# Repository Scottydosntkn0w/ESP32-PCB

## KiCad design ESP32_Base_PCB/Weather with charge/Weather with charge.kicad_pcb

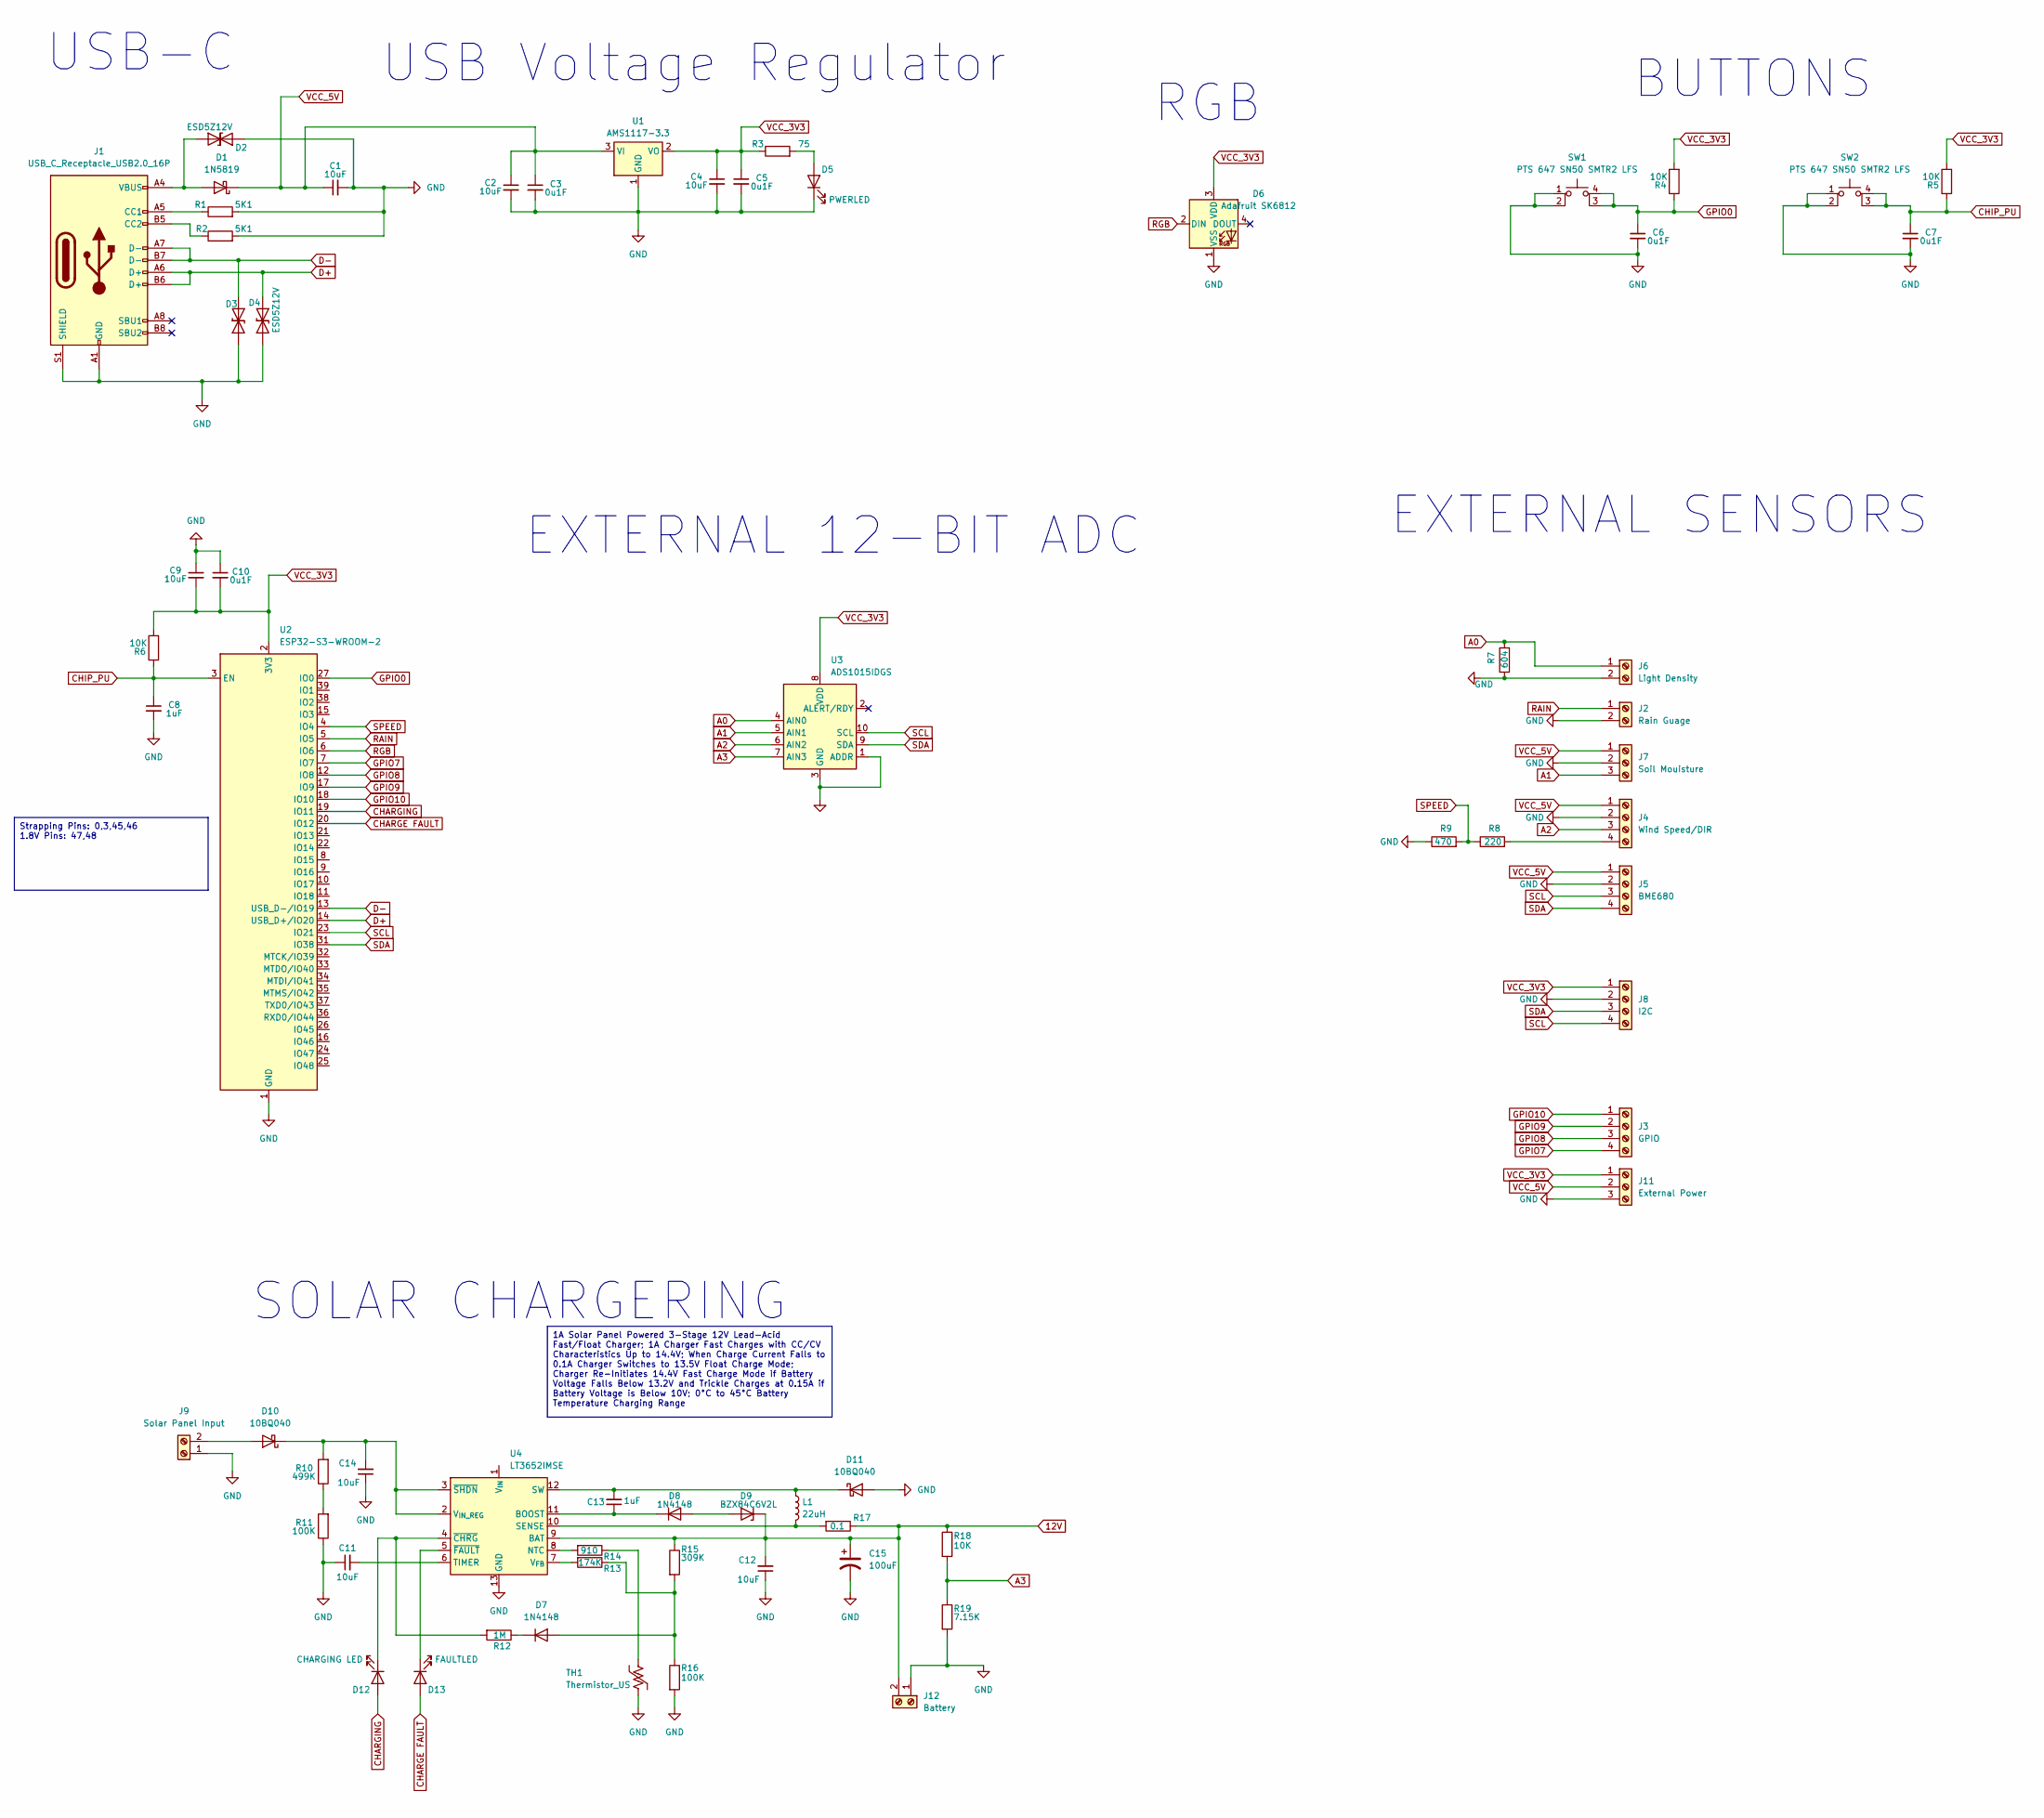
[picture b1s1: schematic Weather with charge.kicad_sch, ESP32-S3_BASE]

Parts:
C1, C2, C4, C9, C11, C12, C14: 10uF; C_0805_2012Metric_Pad1.18x1.45mm_HandSolder; Manufacturer_Part_Number 0805W106K500CC
C3, C5, C6, C7, C10: 0u1F; C_0805_2012Metric_Pad1.18x1.45mm_HandSolder; Manufacturer_Part_Number 0805B104K101CC
C8: 1uF; C_0805_2012Metric_Pad1.18x1.45mm_HandSolder; Manufacturer_Part_Number 0805B105K250DC
C13: 1uF; C_0805_2012Metric_Pad1.18x1.45mm_HandSolder; Manufacturer_Part_Number 0805W106K500CC
C15: 100uF
D1: 1N5819; D_DO-41_SOD81_P10.16mm_Horizontal; Manufacturer_Part_Number 1N5819
D2, D3, D4: ESD5Z12V; D_SOD-523; Manufacturer_Part_Number ESD5Z12V
D5: PWERLED; LED_0603_1608Metric; Manufacturer_Part_Number 0603GBD0790S01
D6: Adafruit SK6812; LED_SK6812_PLCC4_5.0x5.0mm_P3.2mm; Manufacturer_Part_Number 1655
D7, D8: 1N4148; D_DO-35_SOD27_P7.62mm_Horizontal
D9: BZX84C6V2L; SOT-23
D10, D11: 10BQ040; D_SMA; Manufacturer_Part_Number 10BQ040
D12: CHARGING LED; LED_0603_1608Metric; Manufacturer_Part_Number 0603GBD0790S01
D13: FAULTLED; LED_0603_1608Metric; Manufacturer_Part_Number 0603GBD0790S01
J1: USB_C_Receptacle_USB2.0_16P; USB_C_Receptacle_GCT_USB4105-xx-A_16P_TopMnt_Horizontal; Manufacturer_Part_Number USB4105-GF-A
J2: Rain Guage; TerminalBlock_Phoenix_MKDS-1,5-2-5.08_1x02_P5.08mm_Horizont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; Manufacturer_Part_Number 282837-2
J3: GPIO; TerminalBlock_Phoenix_MKDS-1,5-4-5.08_1x04_P5.08mm_Horizont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; Manufacturer_Part_Number 282837-4
J4: Wind Speed/DIR; TerminalBlock_Phoenix_MKDS-1,5-4-5.08_1x04_P5.08mm_Horizont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; Manufacturer_Part_Number 282837-4
J5: BME680; TerminalBlock_Phoenix_MKDS-1,5-4-5.08_1x04_P5.08mm_Horizont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; Manufacturer_Part_Number 282837-4
J6: Light Density; TerminalBlock_Phoenix_MKDS-1,5-2-5.08_1x02_P5.08mm_Horizont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; Manufacturer_Part_Number 282837-2
J7: Soil Mouisture; TerminalBlock_Phoenix_MKDS-1,5-3-5.08_1x03_P5.08mm_Horizont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; Manufacturer_Part_Number 282837-3
J8: I2C; TerminalBlock_Phoenix_MKDS-1,5-4-5.08_1x04_P5.08mm_Horizont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; Manufacturer_Part_Number 282837-4
J9: Solar Panel Input; TerminalBlock_Phoenix_MKDS-1,5-2-5.08_1x02_P5.08mm_Horizont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; Manufacturer_Part_Number 282837-2
J11: External Power; TerminalBlock_Phoenix_MKDS-1,5-3-5.08_1x03_P5.08mm_Horizont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; Manufacturer_Part_Number 282837-3
J12: Battery; TerminalBlock_Phoenix_MKDS-1,5-2-5.08_1x02_P5.08mm_Horizont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; Manufacturer_Part_Number 282837-2
L1: 22uH; Manufacturer_Part_Number 7447779122
R1, R2: 5K1; R_0603_1608Metric_Pad0.98x0.95mm_HandSolder; Manufacturer_Part_Number RC0603FR-075K1L
R3: 75; R_0603_1608Metric_Pad0.98x0.95mm_HandSolder; Manufacturer_Part_Number RC0603FR-0775RL
R4, R5, R6: 10K; R_0603_1608Metric_Pad0.98x0.95mm_HandSolder; Manufacturer_Part_Number RC0603FR-0710KL
R7: 604; R_Axial_DIN0207_L6.3mm_D2.5mm_P10.16mm_Horizontal
R8: 220; R_0603_1608Metric_Pad0.98x0.95mm_HandSolder; Manufacturer_Part_Number RMCF0603JT220R
R9: 470; R_0603_1608Metric_Pad0.98x0.95mm_HandSolder; Manufacturer_Part_Number RL0603FR-070R47L
R10: 499K; R_0603_1608Metric_Pad0.98x0.95mm_HandSolder; Manufacturer_Part_Number RC0603FR-0775RL
R11, R16: 100K; R_0603_1608Metric_Pad0.98x0.95mm_HandSolder; Manufacturer_Part_Number RC0603FR-0775RL
R12: 1M; R_0603_1608Metric_Pad0.98x0.95mm_HandSolder; Manufacturer_Part_Number RC0603FR-0775RL
R13: 174K; R_0603_1608Metric_Pad0.98x0.95mm_HandSolder; Manufacturer_Part_Number RC0603FR-0775RL
R14: 910; R_0603_1608Metric_Pad0.98x0.95mm_HandSolder; Manufacturer_Part_Number RC0603FR-0775RL
R15: 309K; R_0603_1608Metric_Pad0.98x0.95mm_HandSolder; Manufacturer_Part_Number RC0603FR-0775RL
R17: 0.1; R_0603_1608Metric_Pad0.98x0.95mm_HandSolder; Manufacturer_Part_Number RC0603FR-0775RL
R18: 10K; R_0603_1608Metric_Pad0.98x0.95mm_HandSolder; Manufacturer_Part_Number RC0603FR-0775RL
R19: 7.15K; R_0603_1608Metric_Pad0.98x0.95mm_HandSolder; Manufacturer_Part_Number RC0603FR-0775RL
SW1, SW2: PTS 647 SN50 SMTR2 LFS; SW_PTS_647_SN50_SMTR2_LFS; Manufacturer_Part_Number PTS 647 SN50 SMTR2 LFS
TH1: Thermistor_US; R_0603_1608Metric; Manufacturer_Part_Number NCP18XH103F0SRB
U1: AMS1117-3.3; SOT-223-3_TabPin2; Manufacturer_Part_Number AMS1117-3.3
U2: ESP32-S3-WROOM-2; Manufacturer_Part_Number ESP32-S3-WROOM-2-N32R8V
U3: ADS1015IDGS; TSSOP-10_3x3mm_P0.5mm; Manufacturer_Part_Number ADS1015IDGS
U4: LT3652IMSE; MSOP-12-1EP_3x4mm_P0.65mm_EP1.65x2.85mm; Manufacturer_Part_Number LT3652HVIMSE#TRPBF

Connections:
12V: C12.2, C15.1, D9.3 (K), J12.2, R15.1, R17.1, R18.1, U4.9 (BAT)
A0: J6.1, R7.2, U3.4 (AIN0)
A1: J7.3, U3.5 (AIN1)
A2: J4.3, U3.6 (AIN2)
A3: R18.2, R19.1, U3.7 (AIN3); also elsewhere on the board
CHARGE FAULT: D13.1 (K), D13.2 (A), U2.20 (IO12), U4.5 (~FAULT)
CHIP_PU: C7.1, C8.1, R5.1, R6.1, SW2.3 (K), SW2.4 (A), U2.3 (EN)
D+: D4.2 (A), J1.A6 (D+), J1.B6 (D+), U2.14 (USB_D+/IO20)
D-: D3.2 (A), J1.A7 (D-), J1.B7 (D-), U2.13 (USB_D-/IO19)
GND: C1.2, C2.2, C3.2, C4.2, C5.2, C6.2, C7.2, C8.2, C9.1, C10.1, C11.1, C12.1, C14.1, C15.2, D2.1 (K), D3.1 (K), D4.1 (K), D5.1 (K), D6.1 (VSS), D11.2 (A), J1.A1 (GND), J1.A12 (GND), J1.B1 (GND), J1.B12 (GND), J1.S1 (SHIELD), J2.2, J4.2, J5.2, J6.2, J7.2, J8.2, J9.1, J11.3, J12.1, R1.2, R2.2, R7.1, R9.1, R11.1, R16.2, R19.2, SW1.1, SW1.2, SW2.1, SW2.2, TH1.2, U1.1 (GND), U2.1 (GND), U2.40 (GND), U2.41 (GND), U3.1 (ADDR), U3.3 (GND), U4.13 (GND); also elsewhere on the board
GPIO0: C6.1, R4.1, SW1.3 (K), SW1.4 (A), U2.27 (IO0)
GPIO7: J3.4, U2.7 (IO7)
GPIO8: J3.3, U2.12 (IO8)
GPIO9: J3.2, U2.17 (IO9)
GPIO10: J3.1, U2.18 (IO10)
unnamed: D1.2 (A), D2.2 (A), J1.A4 (VBUS), J1.A9 (VBUS), J1.B4 (VBUS), J1.B9 (VBUS)
unnamed: D5.2 (A), R3.2
unnamed: D7.2 (A), R13.1, R15.2, R16.1
unnamed: D7.1 (K), R12.1
unnamed: D8.2 (A), D9.1 (A)
unnamed: C13.1, D8.1 (K), U4.11 (BOOST)
unnamed: D10.2 (A), J9.2
unnamed: C14.2, D10.1 (K), R10.2, U4.2 (V_{IN_REG}), U4.3 (~SHDN)
unnamed: C13.2, D11.1 (K), L1.1, U4.12 (SW)
unnamed: J1.A5 (CC1), R1.1
unnamed: J1.B5 (CC2), R2.1
unnamed: J4.4, R8.2
unnamed: R10.1, R11.2
unnamed: R14.1, TH1.1
unnamed: R14.2, U4.8 (NTC)
unnamed: L1.2, R17.2, U4.10 (SENSE)
unnamed: C11.2, U4.6 (TIMER)
unnamed: R13.2, U4.7 (V_{FB})
RAIN: J2.1, U2.5 (IO5)
RGB: D6.2 (DIN), U2.6 (IO6)
SCL: J5.3, J8.4, U2.23 (IO21), U3.10 (SCL)
SDA: J5.4, J8.3, U2.31 (IO38), U3.9 (SDA)
SPEED: R8.1, R9.2, U2.4 (IO4)
VCC_3V3: C4.1, C5.1, C9.2, C10.2, D6.3 (VDD), J8.1, J11.1, R3.1, R4.2, R5.2, R6.2, U1.2 (VO), U2.2 (3V3), U3.8 (VDD)
VCC_5V: C1.1, C2.1, C3.1, D1.1 (K), J4.1, J5.1, J7.1, J11.2, U1.3 (VI); also elsewhere on the board

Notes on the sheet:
1A Solar Panel Powered 3-Stage 12V Lead-Acid Fast/Float Charger; 1A Charger Fast Charges with CC/CV Characteristics Up to 14.4V; When Charge Current Falls to 0.1A Charger Switches to 13.5V Float Charge Mode; Charger Re-Initiates 14.4V Fast Charge Mode if Battery Voltage Falls Below 13.2V and Trickl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
Strapping Pins: 0,3,45,46 1.8V Pins: 47,48
USB-C
RGB
EXTERNAL SENSORS
SOLAR CHARGERING
USB Voltage Regulator
BUTTONS
EXTERNAL 12-BIT ADC

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
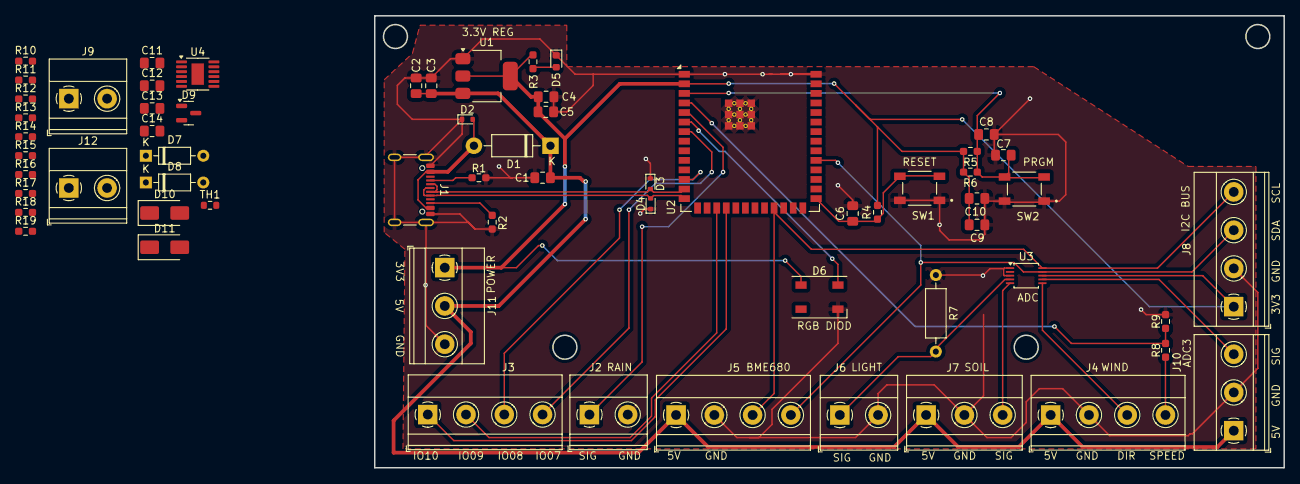
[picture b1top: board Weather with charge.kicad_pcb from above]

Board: 2 copper layers, 120.8 x 60.0 mm, 63 parts (0 on the bottom side), 41 nets.

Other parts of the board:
J10: A3 of ADC; TerminalBlock_Phoenix_MKDS-1,5-3-5.08_1x03_P5.08mm_Horizont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

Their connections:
A3: J10.3; also elsewhere on the board
GND: J10.2; also elsewhere on the board
VCC_5V: J10.1; also elsewhere on the board

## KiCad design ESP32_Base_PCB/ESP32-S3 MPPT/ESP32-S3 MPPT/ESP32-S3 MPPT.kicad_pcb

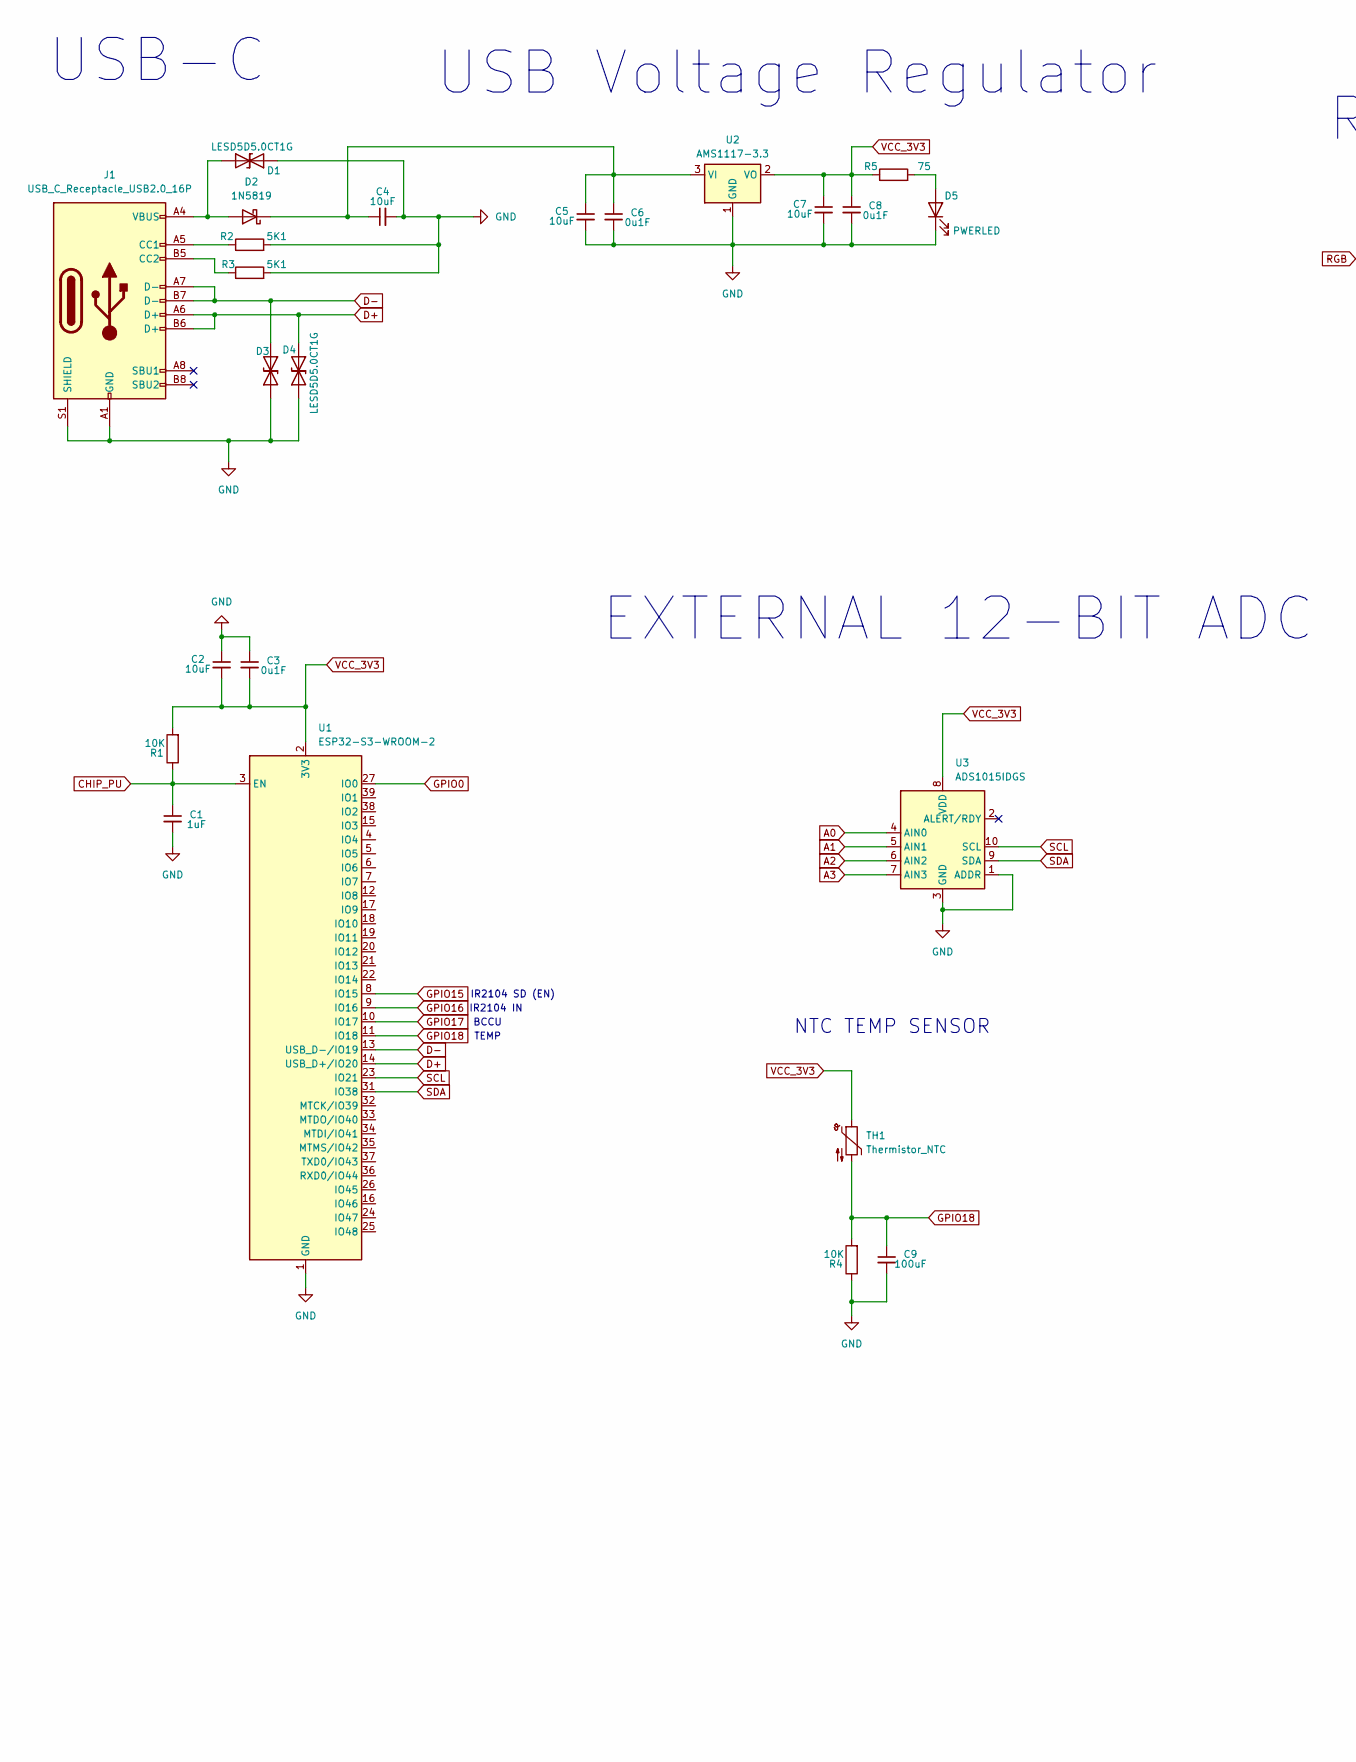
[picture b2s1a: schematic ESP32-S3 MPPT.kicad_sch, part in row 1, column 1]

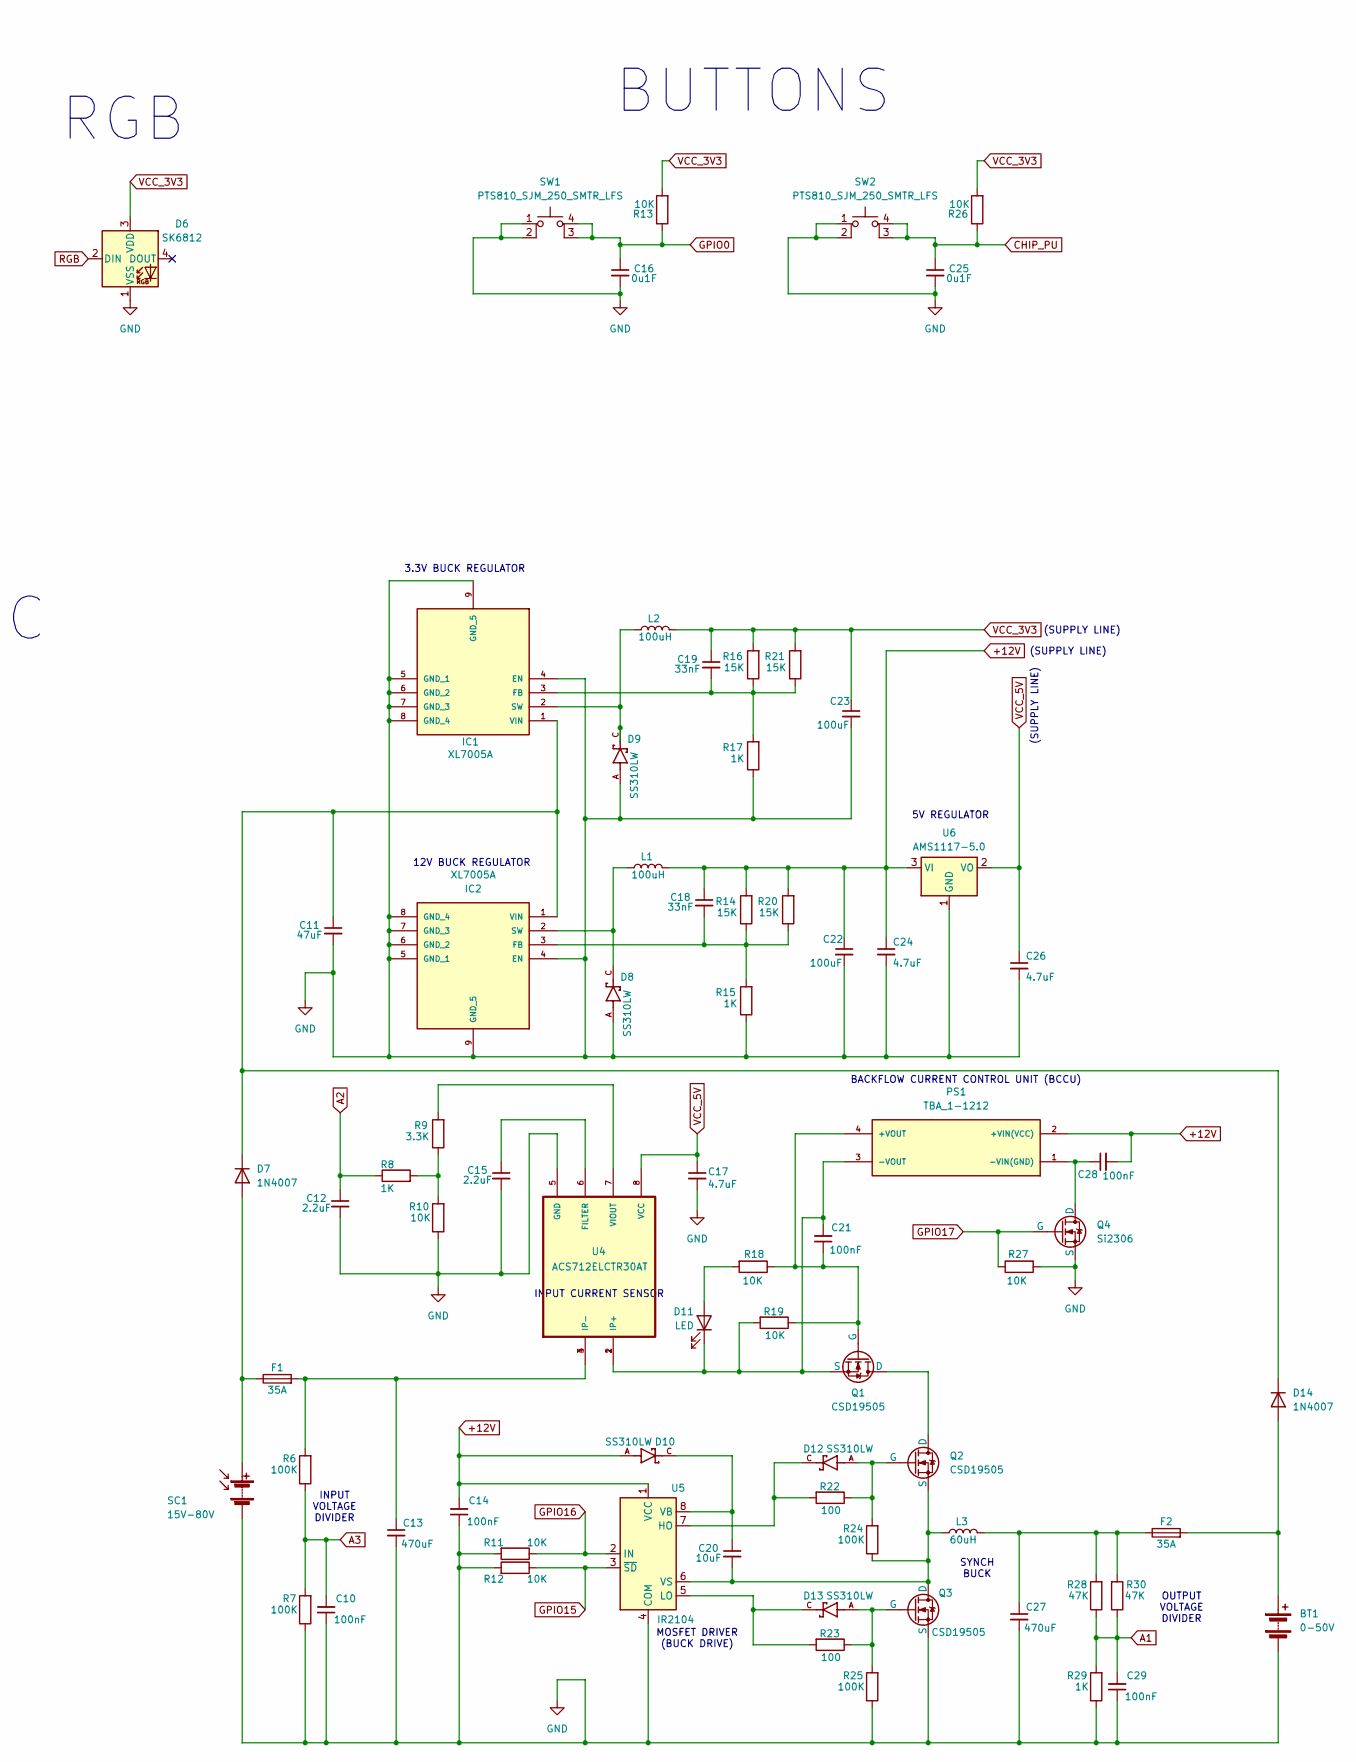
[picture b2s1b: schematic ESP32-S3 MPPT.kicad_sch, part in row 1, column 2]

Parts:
BT1: 0-50V; TerminalBlock_MetzConnect_Type703_RT10N02HGLU_1x02_P9.52mm_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
C1: 1uF; C_0805_2012Metric_Pad1.18x1.45mm_HandSolder
C2, C4, C5, C7, C20: 10uF; C_0805_2012Metric_Pad1.18x1.45mm_HandSolder
C3, C6, C8, C16, C25: 0u1F; C_0805_2012Metric_Pad1.18x1.45mm_HandSolder
C9, C22, C23: 100uF; C_0805_2012Metric_Pad1.18x1.45mm_HandSolder
C10, C14, C21, C28, C29: 100nF; C_0805_2012Metric_Pad1.18x1.45mm_HandSolder
C11: 47uF; C_0805_2012Metric_Pad1.18x1.45mm_HandSolder
C12, C15: 2.2uF; C_0805_2012Metric_Pad1.18x1.45mm_HandSolder
C13, C27: 470uF; CP_Radial_D16.0mm_P7.50mm
C17, C24, C26: 4.7uF; C_0805_2012Metric_Pad1.18x1.45mm_HandSolder
C18, C19: 33nF; C_0805_2012Metric_Pad1.18x1.45mm_HandSolder
D1, D3, D4: LESD5D5.0CT1G; D_SOD-523
D2: 1N5819; D_DO-41_SOD81_P10.16mm_Horizontal
D5: PWERLED; LED_0603_1608Metric
D6: SK6812; LED_SK6812_PLCC4_5.0x5.0mm_P3.2mm
D7, D14: 1N4007; D_DO-41_SOD81_P10.16mm_Horizontal
D8, D9, D10, D12, D13: SS310LW; SODFL3718X102N; PARTREV C2103
D11: LED; LED_0805_2012Metric_Pad1.15x1.40mm_HandSolder
F1, F2: 35A; Fuseholder_Keystone_3555-2
IC1, IC2: XL7005A; SOIC127P600X175-9N; Manufacturer_Part_Number XL7005A
J1: USB_C_Receptacle_USB2.0_16P; USB_C_Receptacle_GCT_USB4105-xx-A_16P_TopMnt_Horizontal
L1, L2: 100uH; IND_SRR4028-101Y
L3: 60uH; L_Toroid_Vertical_L21.6mm_W11.4mm_P7.62mm_Pulse_KM-3
PS1: TBA_1-1212; CONV_TBA_1-1212
Q1, Q2, Q3: CSD19505; TO-220-3_Vertical
Q4: Si2306; SOT-23_Handsoldering
R1, R4, R10, R11, R12, R13, R18, R19, R26, R27: 10K; R_0603_1608Metric_Pad0.98x0.95mm_HandSolder
R2, R3: 5K1; R_0603_1608Metric_Pad0.98x0.95mm_HandSolder
R5: 75; R_0603_1608Metric_Pad0.98x0.95mm_HandSolder
R6, R7, R24, R25: 100K; R_0603_1608Metric_Pad0.98x0.95mm_HandSolder
R8, R15, R17, R29: 1K; R_0603_1608Metric_Pad0.98x0.95mm_HandSolder
R9: 3.3K; R_0603_1608Metric_Pad0.98x0.95mm_HandSolder
R14, R16, R20, R21: 15K; R_0603_1608Metric_Pad0.98x0.95mm_HandSolder
R22, R23: 100; R_0603_1608Metric_Pad0.98x0.95mm_HandSolder
R28, R30: 47K; R_0603_1608Metric_Pad0.98x0.95mm_HandSolder
SC1: 15V-80V; TerminalBlock_MetzConnect_Type703_RT10N02HGLU_1x02_P9.52mm_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
SW1, SW2: PTS810_SJM_250_SMTR_LFS; SW_PTS810_SJM_250_SMTR_LFS
TH1: Thermistor_NTC; TerminalBlock_bornier-2_P5.08mm
U1: ESP32-S3-WROOM-2
U2: AMS1117-3.3; SOT-223-3_TabPin2
U3: ADS1015IDGS; TSSOP-10_3x3mm_P0.5mm
U4: ACS712ELCTR30AT; SOIC127P600X175-8N; PARTREV 1.0
U5: IR2104; SOIC127P600X175-8N
U6: AMS1117-5.0; SOT-223-3_TabPin2

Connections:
+12V: C14.2, C18.1, C22.1, C24.1, C28.2, D10.A, L1.2, PS1.2 (+VIN(VCC)), R14.2, R20.2, U5.1 (VCC), U6.3 (VI)
A0: U3.4 (AIN0)
A1: C29.2, R28.1, R29.2, R30.1, U3.5 (AIN1)
A2: C12.1, R8.1, U3.6 (AIN2)
A3: C10.2, R6.1, R7.2, U3.7 (AIN3)
CHIP_PU: C1.1, C25.1, R1.1, R26.1, SW2.3 (K), SW2.4 (A), U1.3 (EN)
D+: D4.2 (A), J1.A6 (D+), J1.B6 (D+), U1.14 (USB_D+/IO20)
D-: D3.2 (A), J1.A7 (D-), J1.B7 (D-), U1.13 (USB_D-/IO19)
GND: BT1.2 (-), C1.2, C2.1, C3.1, C4.2, C5.2, C6.2, C7.2, C8.2, C9.2, C10.1, C11.2, C12.2, C13.2, C14.1, C15.2, C16.2, C17.2, C22.2, C23.2, C24.2, C25.2, C26.2, C27.2, C29.1, D1.1 (K), D3.1 (K), D4.1 (K), D5.1 (K), D6.1 (VSS), D8.A, D9.A, IC1.4 (EN), IC1.5 (GND_1), IC1.6 (GND_2), IC1.7 (GND_3), IC1.8 (GND_4), IC1.9 (GND_5), IC2.4 (EN), IC2.5 (GND_1), IC2.6 (GND_2), IC2.7 (GND_3), IC2.8 (GND_4), IC2.9 (GND_5), J1.A1 (GND), J1.A12 (GND), J1.B1 (GND), J1.B12 (GND), J1.S1 (SHIELD), Q3.3 (S), Q4.3 (S), R2.2, R3.2, R4.1, R7.1, R10.1, R11.2, R12.2, R15.1, R17.1, R25.1, R27.2, R29.1, SC1.2 (-), SW1.1, SW1.2, SW2.1, SW2.2, U1.1 (GND), U1.40 (GND), U1.41 (GND), U2.1 (GND), U3.1 (ADDR), U3.3 (GND), U4.5 (GND), U5.4 (COM), U6.1 (GND)
GPIO0: C16.1, R13.1, SW1.3 (K), SW1.4 (A), U1.27 (IO0)
GPIO15: R12.1, U1.8 (IO15), U5.3 (~SD)
GPIO16: R11.1, U1.9 (IO16), U5.2 (IN)
GPIO17: Q4.2 (G), R27.1, U1.10 (IO17)
GPIO18: C9.1, R4.2, TH1.2, U1.11 (IO18)
unnamed: BT1.1 (+), D14.2 (A), F2.2
unnamed: C13.1, F1.2, R6.2, U4.3 (IP-), U4.4 (IP-)
unnamed: C27.1, F2.1, L3.2, R28.2, R30.2
unnamed: D1.2 (A), D2.2 (A), J1.A4 (VBUS), J1.A9 (VBUS), J1.B4 (VBUS), J1.B9 (VBUS)
unnamed: C4.1, C5.1, C6.1, D2.1 (K), U2.3 (VI)
unnamed: D5.2 (A), R5.2
unnamed: D7.2 (A), F1.1, SC1.1 (+)
unnamed: D11.2 (A), R18.2
unnamed: C21.2, D11.1 (K), PS1.3 (-VOUT), Q1.3 (S), R19.2, U4.1 (IP+), U4.2 (IP+)
unnamed: C11.1, D7.1 (K), D14.1 (K), IC1.1 (VIN), IC2.1 (VIN)
unnamed: C19.2, IC1.3 (FB), R16.1, R17.2, R21.1
unnamed: D9.C, IC1.2 (SW), L2.1
unnamed: C18.2, IC2.3 (FB), R14.1, R15.2, R20.1
unnamed: D8.C, IC2.2 (SW), L1.1
unnamed: J1.A5 (CC1), R2.1
unnamed: J1.B5 (CC2), R3.1
unnamed: C21.1, PS1.4 (+VOUT), Q1.2 (G), R18.1, R19.1
unnamed: C28.1, PS1.1 (-VIN(GND)), Q4.1 (D)
unnamed: Q1.1 (D), Q2.1 (D)
unnamed: D12.A, Q2.2 (G), R22.1, R24.2
unnamed: C20.2, L3.1, Q2.3 (S), Q3.1 (D), R24.1, U5.6 (VS)
unnamed: D13.A, Q3.2 (G), R23.1, R25.2
unnamed: R8.2, R9.1, R10.2
unnamed: C15.1, U4.6 (FILTER)
unnamed: R9.2, U4.7 (VIOUT)
unnamed: D12.C, R22.2, U5.7 (HO)
unnamed: D13.C, R23.2, U5.5 (LO)
unnamed: C20.1, D10.C, U5.8 (VB)
RGB: D6.2 (DIN)
SCL: U1.23 (IO21), U3.10 (SCL)
SDA: U1.31 (IO38), U3.9 (SDA)
VCC_3V3: C2.2, C3.2, C7.1, C8.1, C19.1, C23.1, D6.3 (VDD), L2.2, R1.2, R5.1, R13.2, R16.2, R21.2, R26.2, TH1.1, U1.2 (3V3), U2.2 (VO), U3.8 (VDD)
VCC_5V: C17.1, C26.1, U4.8 (VCC), U6.2 (VO)

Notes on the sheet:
TEMP
3.3V BUCK REGULATOR
IR2104 IN
SYNCH BUCK
USB Voltage Regulator
NTC TEMP SENSOR
RGB
(SUPPLY LINE)
12V BUCK REGULATOR
INPUT VOLTAGE DIVIDER
EXTERNAL 12-BIT ADC
INPUT CURRENT SENSOR
OUTPUT VOLTAGE DIVIDER
BACKFLOW CURRENT CONTROL UNIT (BCCU)
5V REGULATOR
USB-C
MOSFET DRIVER (BUCK DRIVE)
BUTTONS
BCCU
IR2104 SD (EN)

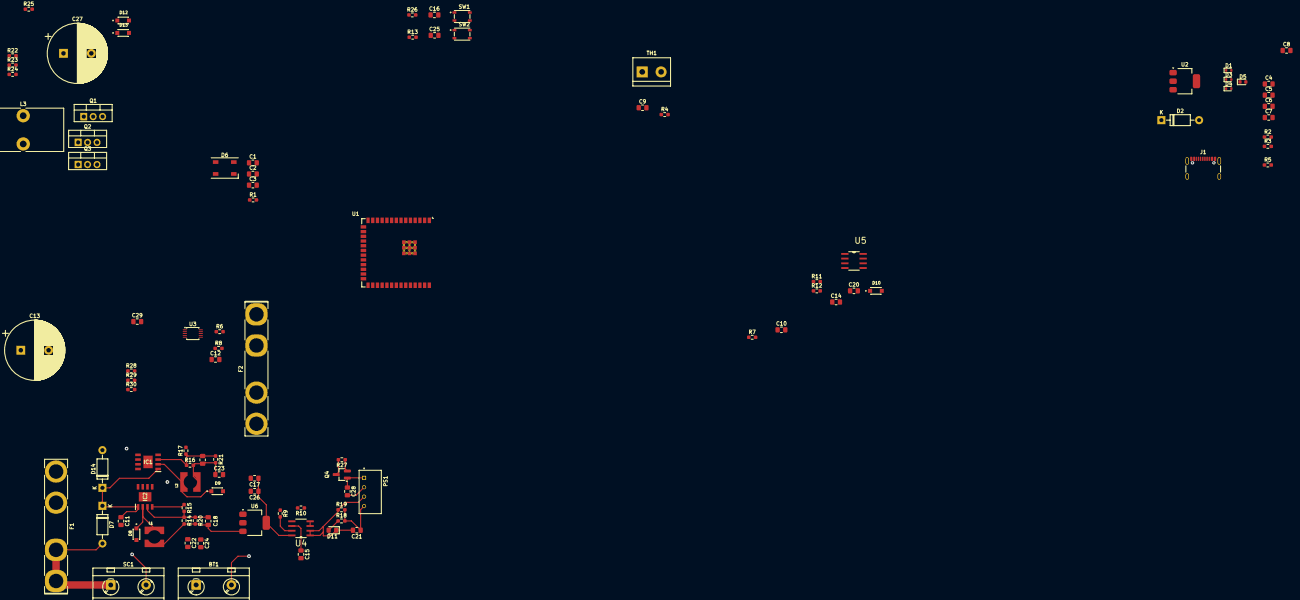
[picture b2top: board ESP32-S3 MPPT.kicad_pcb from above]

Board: 2 copper layers, 97 parts (0 on the bottom side), 45 nets.

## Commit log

2024-02-28 Created Base ESP-32 Board
    Created Base ESP-32 Board
2024-02-28 started Weather station PCB
2024-03-01 removed rescources
2024-03-01 more changes
2024-03-05 v2 weather station
2024-03-06 Created GRBR File
2024-03-06 stuff at home
2024-03-07 now?
